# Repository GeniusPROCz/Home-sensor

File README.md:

# Home-sensor

## Licence

Tento projekt je licencován pod licencí **Creative Commons Attribution-NonCommercial 4.0 International (CC BY-NC 4.0)**.

### Co to znamená:
* **Sdílení:** Můžete projekt šířit a kopírovat v jakémkoliv formátu.
* **Úpravy:** Můžete projekt měnit, doplňovat a stavět na něm.
* **Uvedení autora:** Musíte uvést autora a odkaz na původní projekt.
* **Nekomerční užití:** Nesmíte tento projekt ani jeho části využívat pro komerční účely (prodej produktu, placené služby atd.).

Úplné znění licence naleznete [zde](https://creativecommons.org/licenses/by-nc/4.0/legalcode.cs).

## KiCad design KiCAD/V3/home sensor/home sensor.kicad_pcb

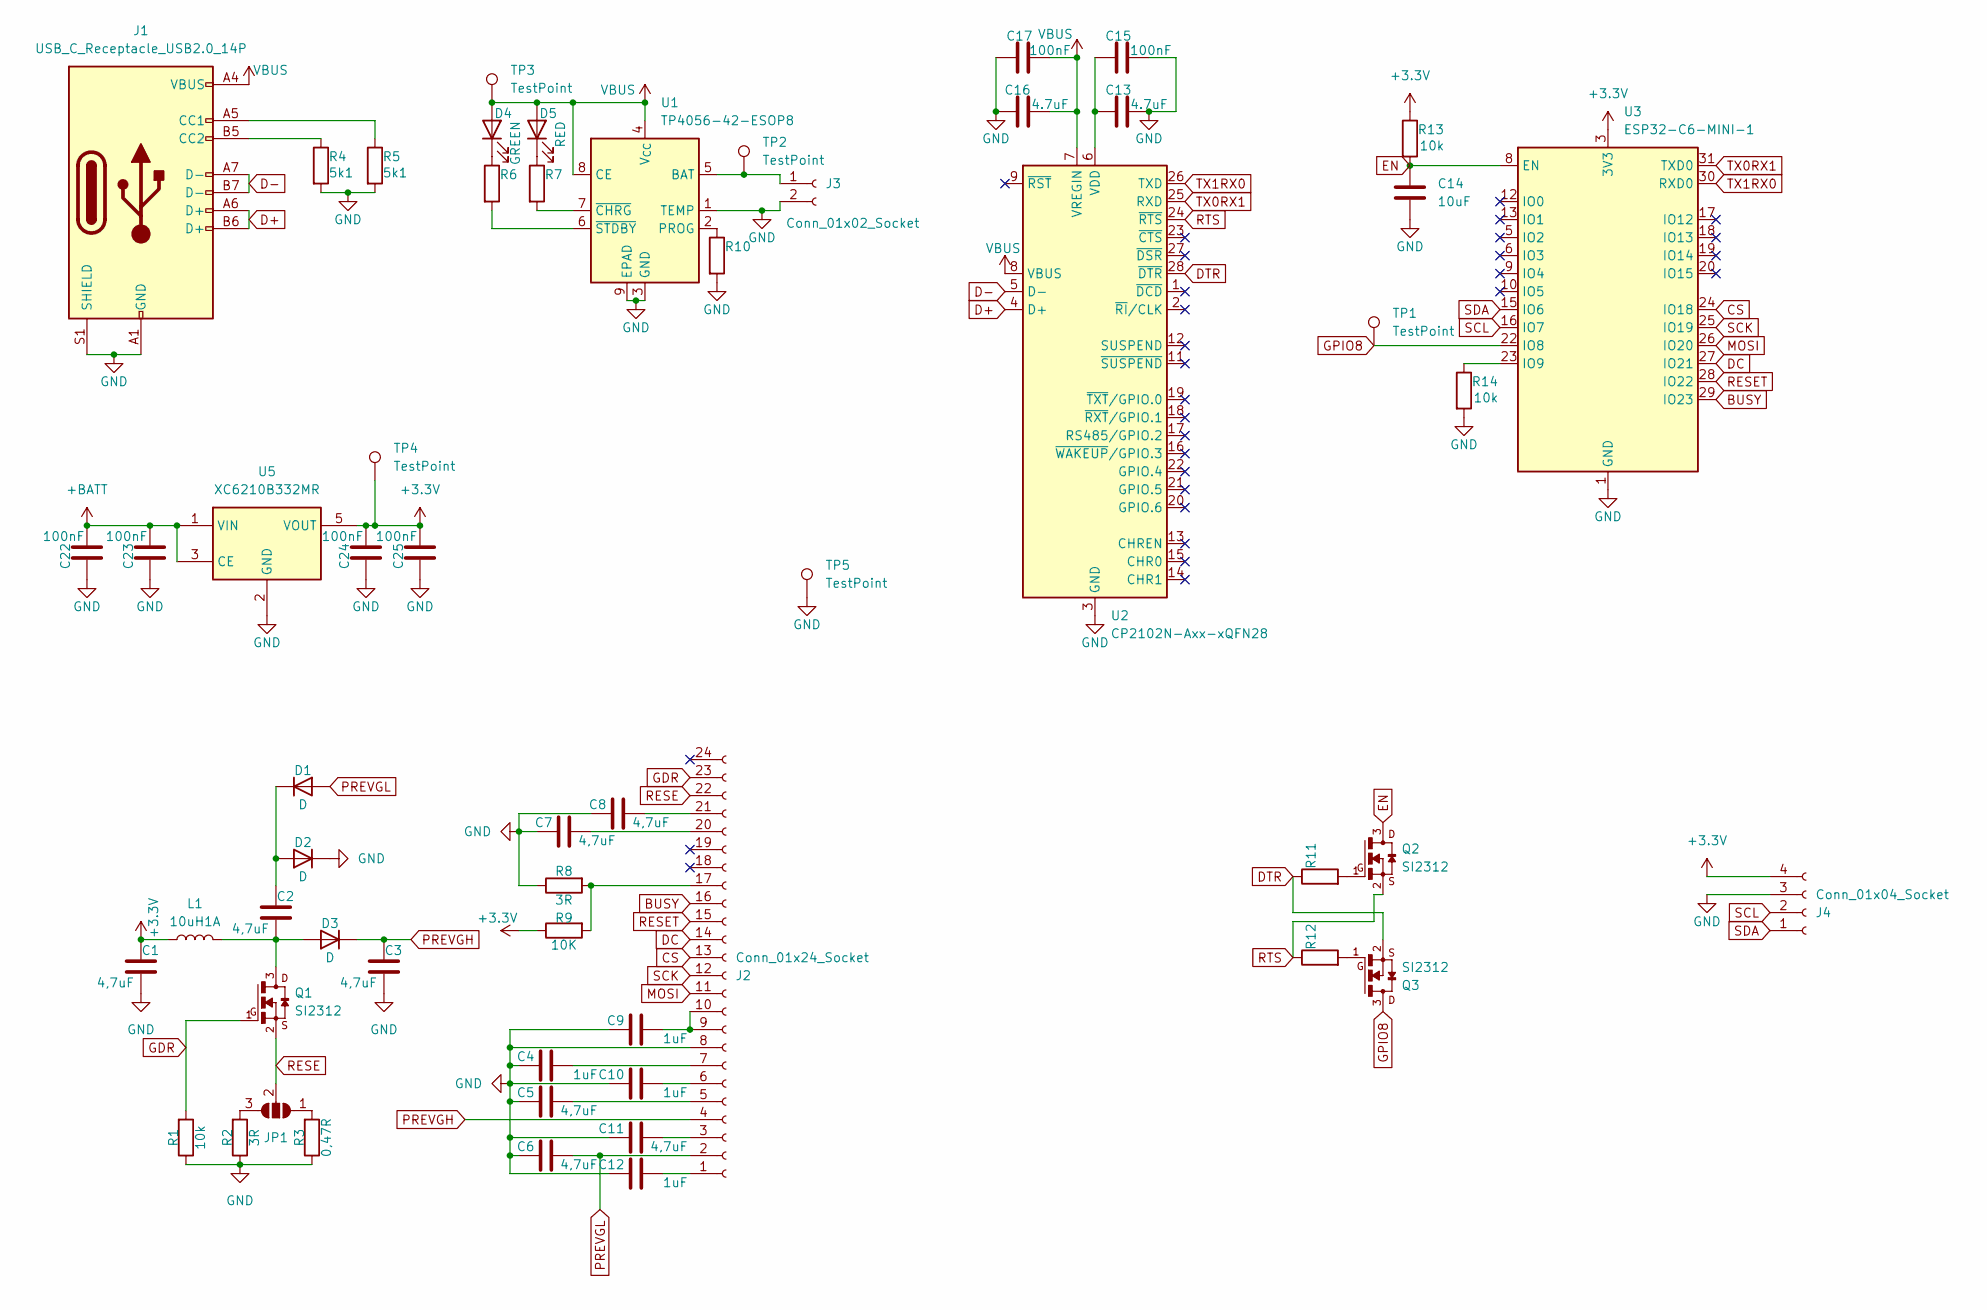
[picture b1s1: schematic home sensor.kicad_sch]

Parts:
C1, C2, C3, C5, C6, C7, C8, C11: 4,7uF; C_0805_2012Metric_Pad1.18x1.45mm_HandSolder
C4, C9, C10, C12: 1uF; C_0805_2012Metric_Pad1.18x1.45mm_HandSolder
C13, C16: 4.7uF; C_0805_2012Metric_Pad1.18x1.45mm_HandSolder
C14: 10uF; C_0805_2012Metric_Pad1.18x1.45mm_HandSolder
C15, C17, C22, C23, C24, C25: 100nF; C_0805_2012Metric_Pad1.18x1.45mm_HandSolder
D1, D2, D3: D; D_SOD-123
D4: GREEN; LED_0805_2012Metric_Pad1.15x1.40mm_HandSolder
D5: RED; LED_0805_2012Metric_Pad1.15x1.40mm_HandSolder
J1: USB_C_Receptacle_USB2.0_14P; USB_C_Receptacle_G-Switch_GT-USB-7010ASV_model
J2: Conn_01x24_Socket; Amphenol_F32R-1A7x1-11024_1x24-1MP_P0.5mm_Horizontal
J3: Conn_01x02_Socket; JST_PH_S2B-PH-K_1x02_P2.00mm_Horizontal
J4: Conn_01x04_Socket; PinSocket_1x04_P2.54mm_Horizontal
JP1: SolderJumper_3_Open; SolderJumper-3_P1.3mm_Open_RoundedPad1.0x1.5mm
L1: 10uH1A; L_7.3x7.3_H4.5
Q1, Q2, Q3: SI2312; SOT23
R1, R13, R14: 10k; R_0805_2012Metric_Pad1.20x1.40mm_HandSolder
R2, R8: 3R; R_0805_2012Metric_Pad1.20x1.40mm_HandSolder
R3: 0,47R; R_0805_2012Metric_Pad1.20x1.40mm_HandSolder
R4, R5: 5k1; R_0805_2012Metric_Pad1.20x1.40mm_HandSolder
R6, R7, R10, R11, R12: R_0805_2012Metric_Pad1.20x1.40mm_HandSolder
R9: 10K; R_0805_2012Metric_Pad1.20x1.40mm_HandSolder
TP1, TP2, TP3, TP4: TestPoint; TestPoint_Pad_D1.5mm
TP5: TestPoint; TestPoint_Bridge_Pitch2.54mm_Drill0.7mm
U1: TP4056-42-ESOP8; SOIC-8-1EP_3.9x4.9mm_P1.27mm_EP2.41x3.3mm_ThermalVias
U2: CP2102N-Axx-xQFN28; QFN-28-1EP_5x5mm_P0.5mm_EP3.35x3.35mm
U3: ESP32-C6-MINI-1
U5: XC6210B332MR; SOT-23-5

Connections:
+3.3V: C1.1, C24.1, C25.1, J4.4, L1.1, R9.1, R13.1, TP4.1, U3.3 (3V3), U5.5 (VOUT)
+BATT: C22.1, C23.1, U5.1 (VIN), U5.3 (CE)
BUSY: J2.16, U3.29 (IO23)
CS: J2.13, U3.24 (IO18)
D+: J1.A6 (D+), J1.B6 (D+), U2.4 (D+)
D-: J1.A7 (D-), J1.B7 (D-), U2.5 (D-)
DC: J2.14, U3.27 (IO21)
DTR: Q3.2, R11.1, U2.28 (~DTR)
EN: C14.1, Q2.3, R13.2, U3.8 (EN)
GDR: J2.23, Q1.1, R1.2
GND: C1.2, C3.2, C4.1, C5.1, C6.1, C7.1, C8.1, C9.1, C10.1, C11.1, C12.1, C13.1, C14.2, C15.1, C16.2, C17.2, C22.2, C23.2, C24.2, C25.2, D2.1 (K), J1.A1 (GND), J1.A12 (GND), J1.B1 (GND), J1.B12 (GND), J1.S1 (SHIELD), J2.8, J3.2, J4.3, R1.1, R2.1, R3.1, R4.2, R5.2, R8.1, R10.2, R14.2, TP5.1, U1.1 (TEMP), U1.3 (GND), U1.9 (EPAD), U2.3 (GND), U2.29 (GND), U3.1 (GND), U3.2 (GND), U3.11 (GND), U3.14 (GND), U3.36 (GND), U3.37 (GND), U3.38 (GND), U3.39 (GND), U3.40 (GND), U3.41 (GND), U3.42 (GND), U3.43 (GND), U3.44 (GND), U3.45 (GND), U3.46 (GND), U3.47 (GND), U3.48 (GND), U3.49 (GND), U3.50 (GND), U3.51 (GND), U3.52 (GND), U3.53 (GND), U5.2 (GND)
GPIO8: Q3.3, TP1.1, U3.22 (IO8)
MOSI: J2.11, U3.26 (IO20)
unnamed: C2.1, D1.1 (K), D2.2 (A)
unnamed: C2.2, D3.2 (A), L1.2, Q1.3
unnamed: D4.1 (K), R6.1
unnamed: D5.1 (K), R7.1
unnamed: J1.A5 (CC1), R5.1
unnamed: J1.B5 (CC2), R4.1
unnamed: C12.2, J2.1
unnamed: C11.2, J2.3
unnamed: C5.2, J2.5
unnamed: C10.2, J2.6
unnamed: C4.2, J2.7
unnamed: C9.2, J2.9, J2.10
unnamed: J2.17, R8.2, R9.2
unnamed: C7.2, J2.20
unnamed: C8.2, J2.21
unnamed: J3.1, TP2.1, U1.5 (BAT)
unnamed: JP1.1 (A), R3.2
unnamed: JP1.3 (B), R2.2
unnamed: Q2.1, R11.2
unnamed: Q3.1, R12.2
unnamed: R10.1, U1.2 (PROG)
unnamed: R7.2, U1.7 (~CHRG)
unnamed: R6.2, U1.6 (~STDBY)
unnamed: C13.2, C15.2, U2.6 (VDD)
unnamed: R14.1, U3.23 (IO9)
PREVGH: C3.1, D3.1 (K), J2.4
PREVGL: C6.2, D1.2 (A), J2.2
RESE: J2.22, JP1.2 (C), Q1.2
RESET: J2.15, U3.28 (IO22)
RTS: Q2.2, R12.1, U2.24 (~RTS)
SCK: J2.12, U3.25 (IO19)
SCL: J4.2, U3.16 (IO7)
SDA: J4.1, U3.15 (IO6)
TX0RX1: U2.25 (RXD), U3.31 (TXD0)
TX1RX0: U2.26 (TXD), U3.30 (RXD0)
VBUS: C16.1, C17.1, D4.2 (A), D5.2 (A), J1.A4 (VBUS), J1.A9 (VBUS), J1.B4 (VBUS), J1.B9 (VBUS), TP3.1, U1.4 (V_{CC}), U1.8 (CE), U2.7 (VREGIN), U2.8 (VBUS)

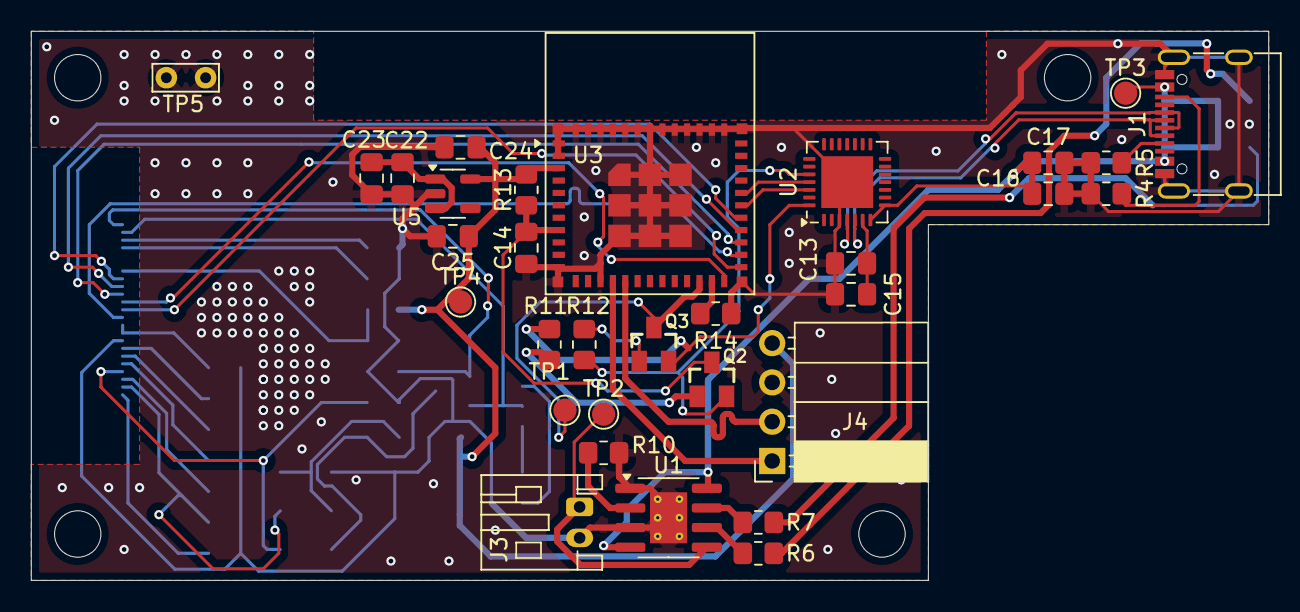
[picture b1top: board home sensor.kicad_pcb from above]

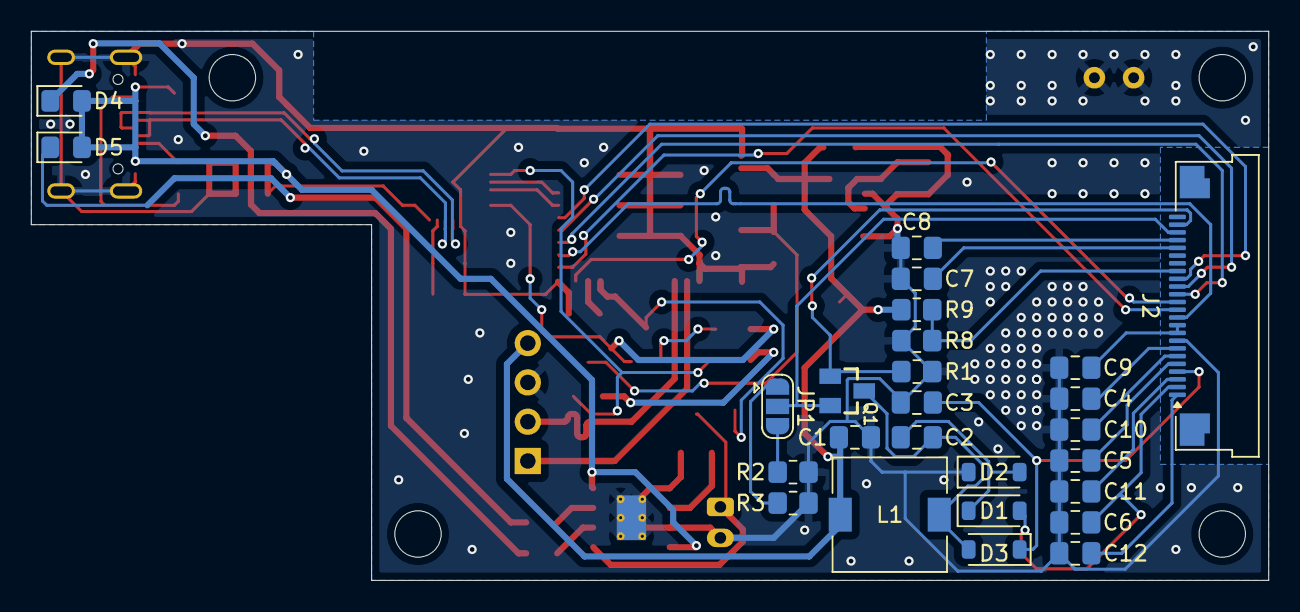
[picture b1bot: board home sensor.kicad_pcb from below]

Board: 2 copper layers, 80.0 x 35.5 mm, 58 parts (26 on the bottom side), 49 nets.

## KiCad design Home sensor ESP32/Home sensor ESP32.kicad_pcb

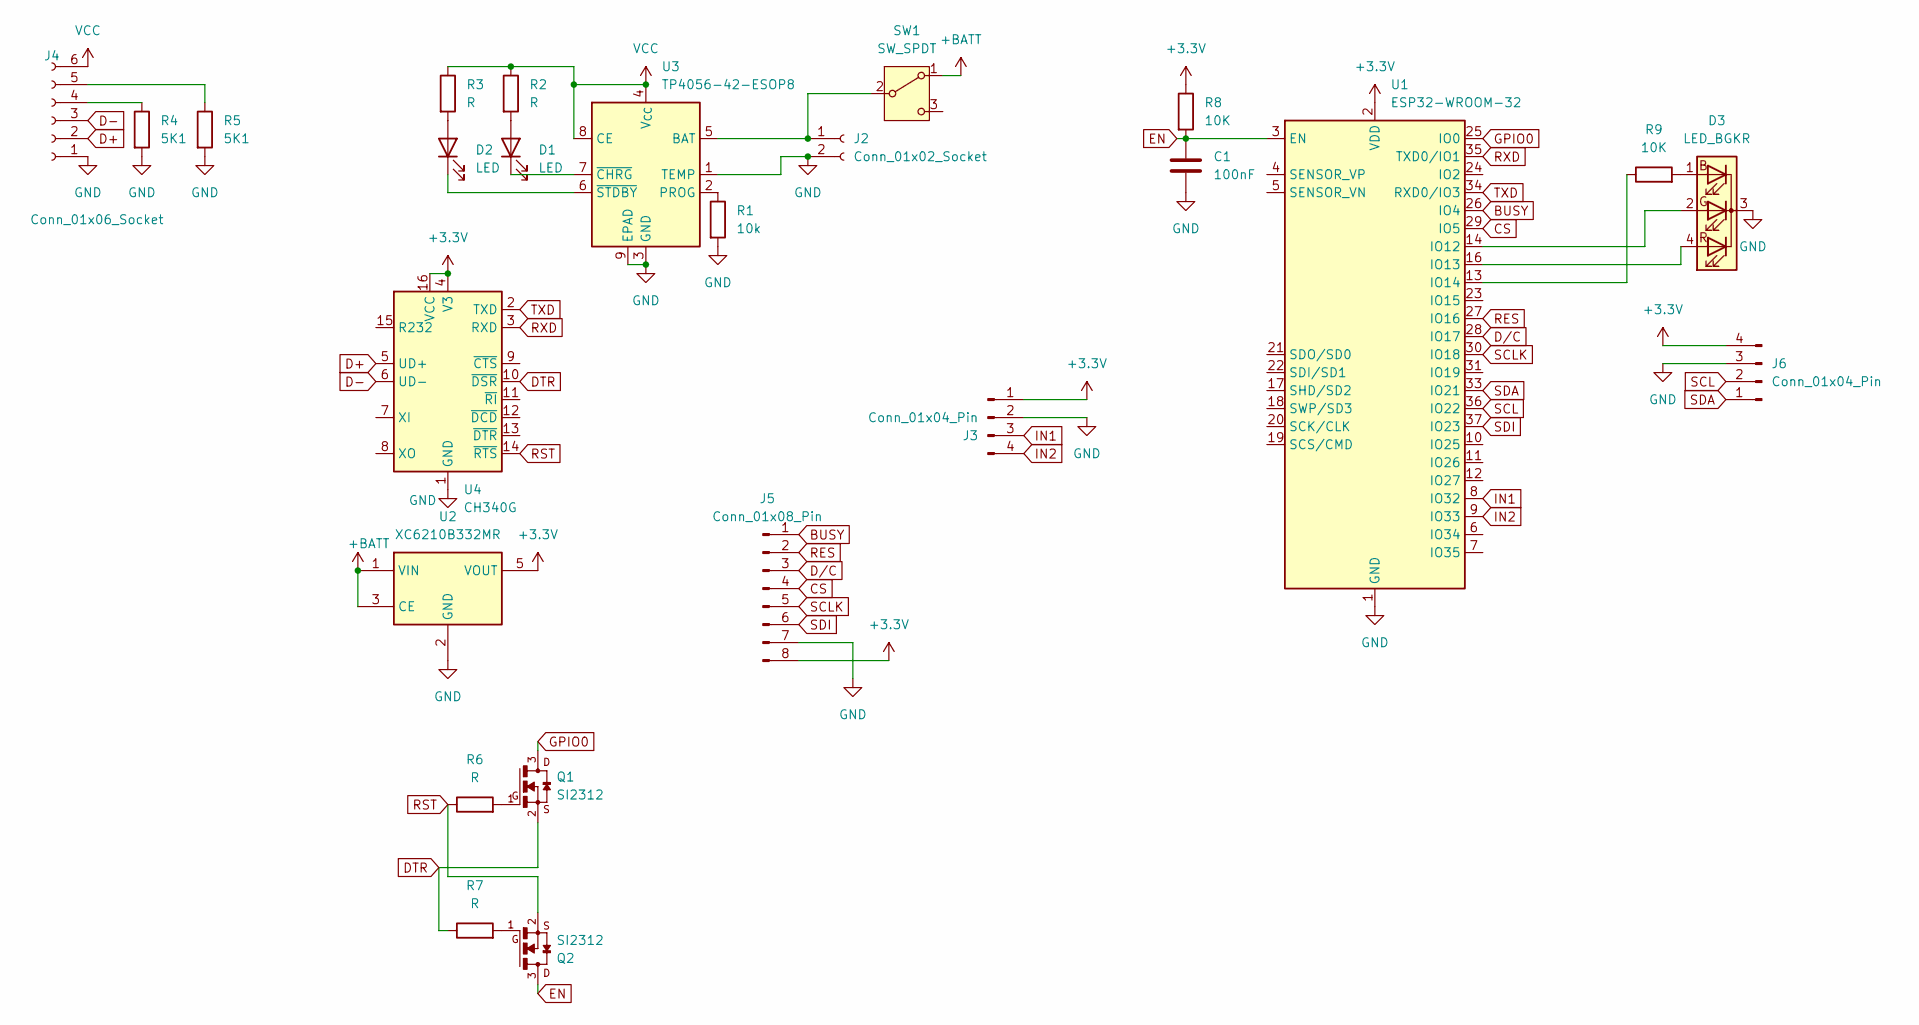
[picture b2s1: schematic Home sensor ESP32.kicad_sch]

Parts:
C1: 100nF; C_0805_2012Metric_Pad1.18x1.45mm_HandSolder
D1, D2: LED; LED_0805_2012Metric_Pad1.15x1.40mm_HandSolder
D3: LED_BGKR; LED_D5.0mm-4_RGB
J2: Conn_01x02_Socket; JST_PH_S2B-PH-K_1x02_P2.00mm_Horizontal
J3: Conn_01x04_Pin; PinHeader_1x04_P2.54mm_Vertical
J4: Conn_01x06_Socket; JST_PH_S6B-PH-K_1x06_P2.00mm_Horizontal
J5: Conn_01x08_Pin; PinHeader_1x08_P2.54mm_Vertical
J6: Conn_01x04_Pin; JST_XH_B4B-XH-AM_1x04_P2.50mm_Vertical
Q1, Q2: SI2312; SOT23
R1: 10k; R_0805_2012Metric_Pad1.20x1.40mm_HandSolder
R2, R3, R6, R7: R; R_0805_2012Metric_Pad1.20x1.40mm_HandSolder
R4, R5: 5K1; R_0805_2012Metric_Pad1.20x1.40mm_HandSolder
R8, R9: 10K; R_0805_2012Metric_Pad1.20x1.40mm_HandSolder
SW1: SW_SPDT; JST_PH_S3B-PH-K_1x03_P2.00mm_Horizontal
U1: ESP32-WROOM-32
U2: XC6210B332MR; SOT-23-5
U3: TP4056-42-ESOP8; SOIC-8-1EP_3.9x4.9mm_P1.27mm_EP2.41x3.3mm_ThermalVias_model
U4: CH340G; SOIC-16_3.9x9.9mm_P1.27mm

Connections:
+3.3V: J3.1, J5.8, J6.4, R8.1, U1.2 (VDD), U2.5 (VOUT), U4.4 (V3), U4.16 (VCC)
+BATT: SW1.1 (A), U2.1 (VIN), U2.3 (CE)
BUSY: J5.1, U1.26 (IO4)
CS: J5.4, U1.29 (IO5)
D+: J4.2, U4.5 (UD+)
D-: J4.3, U4.6 (UD-)
DTR: Q1.2, R7.1, U4.10 (~DSR)
D/C: J5.3, U1.28 (IO17)
EN: C1.1, Q2.3, R8.2, U1.3 (EN)
GND: C1.2, D3.3 (K), J2.2, J3.2, J4.1, J5.7, J6.3, R1.2, R4.2, R5.2, U1.1 (GND), U1.15 (GND), U1.38 (GND), U1.39 (GND), U2.2 (GND), U3.1 (TEMP), U3.3 (GND), U3.9 (EPAD), U4.1 (GND)
GPIO0: Q1.3, U1.25 (IO0)
IN1: J3.3, U1.8 (IO32)
IN2: J3.4, U1.9 (IO33)
unnamed: D1.2 (A), R2.2
unnamed: D1.1 (K), U3.7 (~CHRG)
unnamed: D2.2 (A), R3.2
unnamed: D2.1 (K), U3.6 (~STDBY)
unnamed: D3.1 (BA), R9.2
unnamed: D3.2 (GA), U1.14 (IO12)
unnamed: D3.4 (RA), U1.16 (IO13)
unnamed: J2.1, SW1.2 (B), U3.5 (BAT)
unnamed: J4.4, R4.1
unnamed: J4.5, R5.1
unnamed: Q1.1, R6.2
unnamed: Q2.1, R7.2
unnamed: R9.1, U1.13 (IO14)
unnamed: R1.1, U3.2 (PROG)
RES: J5.2, U1.27 (IO16)
RST: Q2.2, R6.1, U4.14 (~RTS)
RXD: U1.35 (TXD0/IO1), U4.3 (RXD)
SCL: J6.2, U1.36 (IO22)
SCLK: J5.5, U1.30 (IO18)
SDA: J6.1, U1.33 (IO21)
SDI: J5.6, U1.37 (IO23)
TXD: U1.34 (RXD0/IO3), U4.2 (TXD)
VCC: J4.6, R2.1, R3.1, U3.4 (V_{CC}), U3.8 (CE)

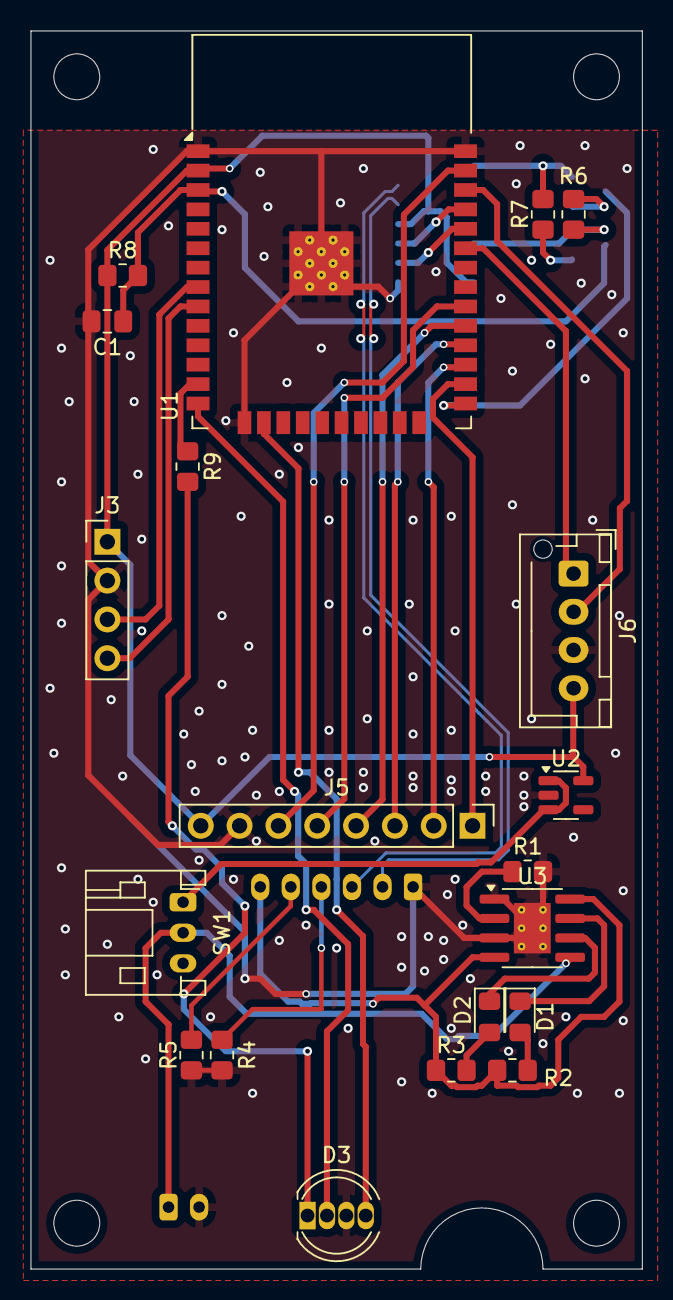
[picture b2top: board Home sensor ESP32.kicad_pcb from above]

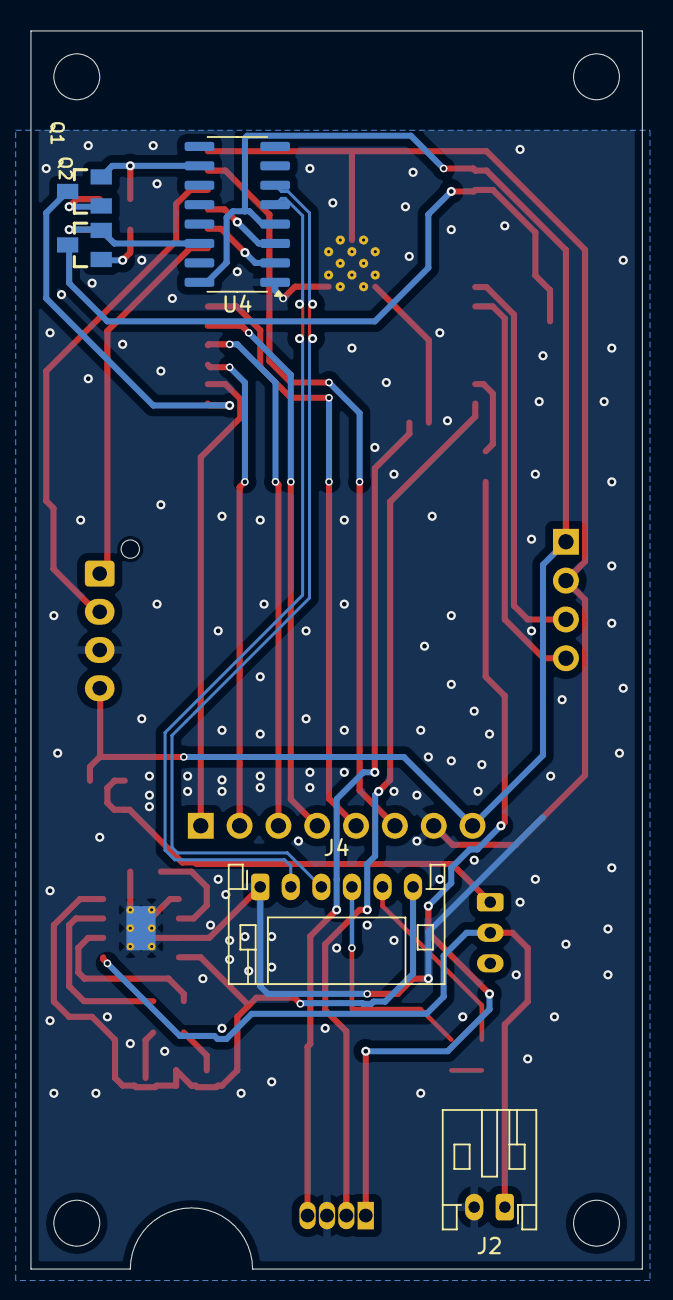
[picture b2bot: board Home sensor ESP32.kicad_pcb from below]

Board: 2 copper layers, 40.0 x 81.0 mm, 25 parts (5 on the bottom side), 36 nets.

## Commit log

2026-01-08 Update README.md
    licencse
2026-01-08 update from home folder
